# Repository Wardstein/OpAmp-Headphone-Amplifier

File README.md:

# Headphone Amplifier with 24bit DAC
A (massive) parallel OpAmp headphone amplifier using 16 parallel OpAmps per channel. The complete box has three PCBs: the power supply, a 24bit DAC with USB interface and the amplifier board itself (hidden under the black heatsink).

The amplifier PSU "base board" has an input for analog signals which can be routed to the amp board, or there can be a USB DAC board plugged in. When you want to switch between analog and USB input, you need to solder a switch to the base board connections of the DAC board (see in the pictures above).

# Noise
The reasoning behind the paralleling so much opamps is to decrease the noise during amplification and therefore improve the SNR. When using this headphone amp with the USB DAC board, we want to give some credit to the 24bit DAC and make the amp as low noise as possible.

In theory the noise is multiplied by the square root of N (number of amplifiers), instead of the number of amplifiers like the gain. Here is a good read: https://www.analog.com/en/technical-articles/paralleling-amplifiers-improves-signal-to-noise-performance.html

This is also the reasoning for the torodial transformer and the linear power supply.

One drawback of the parallel OpAmps is the waste heat, generated by the chips as they are driving their outputs against each other. Typically audio amplifiers are not "high precision" amps in terms of DC offset voltages, so each OpAmp has a different offset and therefore they all drive a bit of current all the time.

# Setting up the CP2114-B02 USB-I2S Bridge chip
Poorly the CP2114-B02 is also obsolete and I could not find any other replacement chip for USB to I2S which offers 24bit support. ONLY the -B02 version offers 24bit support. Maybe one can replace it with some Cypress FX2/FX3 chips or an AVR/SAM with a USB audio device firmware.

Anyways, how to configure the existing CP2114-B02: It has a One-Time Programmable ROM (chapter 3.6 in the datasheet), where config slots can be programmed with a PC tool. These slots contain information about clocking, audio data format and so on. The config is selected at startup by some bootstrapping pins, which means we do not have to configure the CP2114 with an MCU after we programmed it with the PC.

Steps to program the config:

1. Extract the PC utility called CP21xxCustomizationUtility from AN721SW.zip file, for your operating system
2. Connect the DAC board/the CP2114 via USB and power it up (could be in this headphone amplifier, or in your custom circuit)
3. Load the finished configuration from the file "ConfigData_24bit.txt" and click the "Program Device" button.

Ensure you selected the right config at the first time of programming, as each slot can only be written once. The next program cycle will write to the next slot, and you have to change then the config bootstrapping pin resistors to select the right config slot at startup!

After programming the chip, you need to uninstall it in the device manager and replug it, at least under windows, to make the new config take effect.

Some link collection used during the config creation:

* Only 24bit playback or recording at a time:
  * https://community.silabs.com/s/article/cp2114-b02-24-bit-record-playback-vs-16-bit-record-playback?language=en_US
  * https://community.silabs.com/s/article/cp2114-b02-audio-24-bit-mode?language=en_US
  * https://community.silabs.com/s/question/0D51M00007xeOMqSAM/does-the-cp2114b02-support-true-24-bits?language=en_US
* Bad noise (happend to me also), taken care in the config
  * https://community.silabs.com/s/question/0D51M00007xeE9cSAE/cp2114-crackling-or-choppy-noise?language=en_US
  * https://community.silabs.com/s/article/cp2114-and-asynchronous-mode?language=en_US
  * https://www.silabs.com/documents/public/errata/cp2114-errata.pdf chapter 3.2.1
* Distinguishing chip version: https://community.silabs.com/s/article/cp2114-b01-vs-b02-package-marking-1?language=en_US

# Replacement for the obsolete OPA2604
The internet delivers multiple alternatives for the obsolete OPA2604:
* OPA2134 (need to make sure the PSU PCB is tuned to +-15V!)
* OPA2227 (need to make sure the PSU PCB is tuned to +-15V!)
* OPA1642
* NE5534A (not a double opamp, not pin compatible)

Source: http://www.hifi-forum.de/viewthread-71-13538.html (german). Also with some good noise comparison charts.

# Housing

The housing is a proMa "Euro-Gehäuse EG 1" article number "131 020", e.g. available at [Reichelt](https://www.reichelt.de/de/en/euro-casing-geh-eg-1-p50423.html). The front and back are custom 3D prints. The front panel PCB is also custom made exactly for this housing, but is fairly easy modified for any other housing front.

# License
The content of this whole repository is licensed under [CERN-OHL-W v2](License/cern_ohl_w_v2.txt) or later by Jonas Eberhard.

Excepted is the software copied from Cypress in the AN721SW.zip file. This was copied to this repo for archiving purpose!

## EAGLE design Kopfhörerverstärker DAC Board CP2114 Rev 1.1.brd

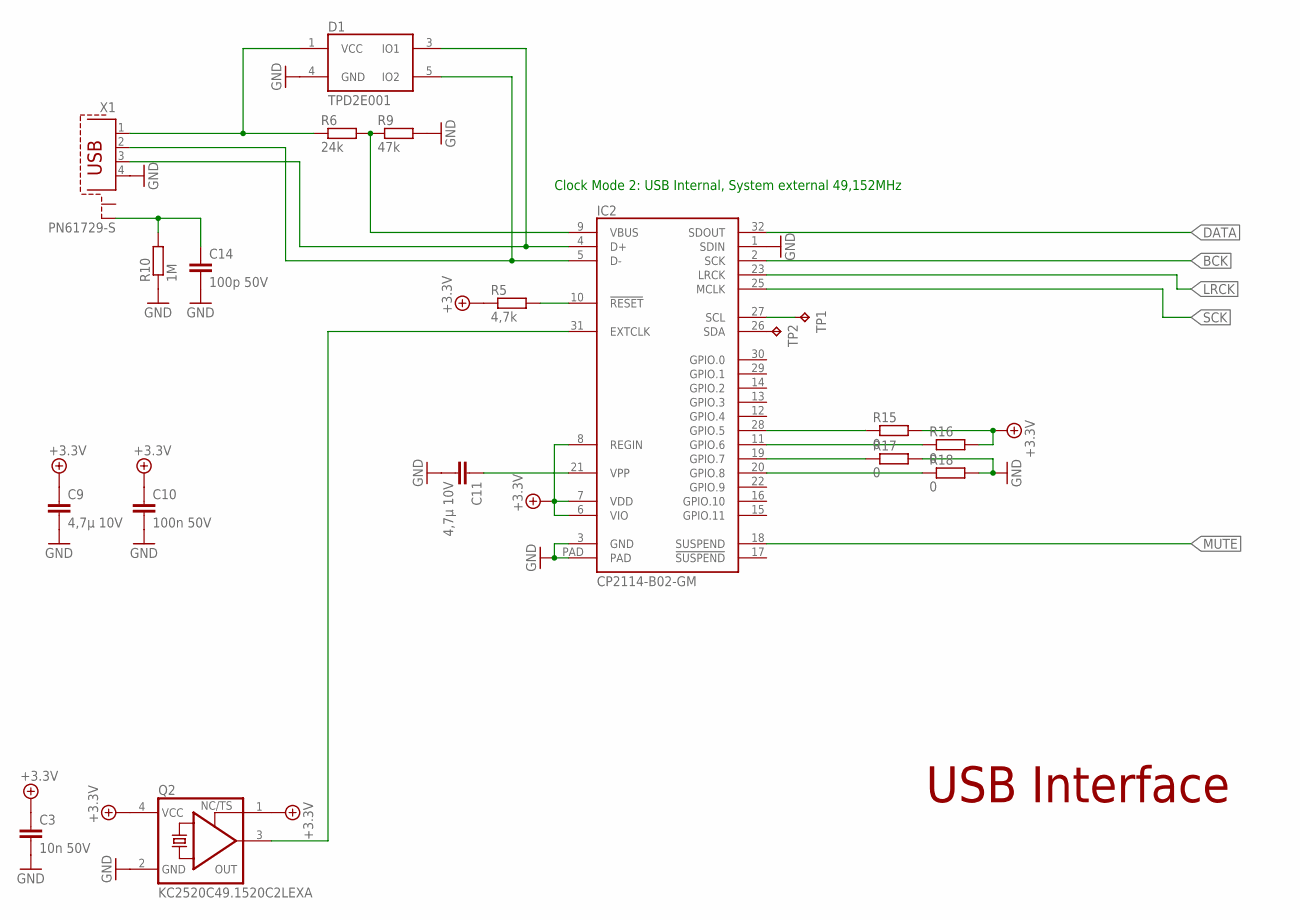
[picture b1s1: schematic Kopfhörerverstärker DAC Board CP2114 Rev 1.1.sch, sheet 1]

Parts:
C3: 10n 50V; C0805
C9, C11: 4,7µ 10V; C0805
C10: 100n 50V; C0805
C14: 100p 50V; C0805
D1: TPD2E001; SOT-5X3_R-PDSO-N5-DRL
IC2: CP2114-B02-GM; QFN32
Q2: KC2520C49.1520C2LEXA; 2.5X2.0
R5: 4,7k; R0805
R6: 24k; R0805
R9: 47k; R0805
R10: 1M; R0805
R15, R16, R17, R18: 0; R0805
TP1, TP2: TPTP10R; TP10R
X1: PN61729-S

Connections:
+3,3V: C3.1, C9.1, C10.1, IC2.6 (VIO), IC2.7 (VDD), IC2.8 (REGIN), Q2.1 (TS), Q2.4 (VCC), R5.1, R15.2, R16.2; also elsewhere on the board
BCK: IC2.2 (SCK); also elsewhere on the board
DATA: IC2.32 (SDOUT); also elsewhere on the board
GND: C3.2, C9.2, C10.2, C11.2, C14.2, D1.4 (GND), IC2.1 (SDIN), IC2.3 (GND), IC2.PAD, Q2.2 (GND), R9.2, R10.1, R17.2, R18.2, X1.4; also elsewhere on the board
LRCK: IC2.23 (LRCK); also elsewhere on the board
MUTE: IC2.18 (SUSPEND); also elsewhere on the board
unnamed: IC2.28 (GPIO.5), R15.1
unnamed: IC2.31 (EXTCLK), Q2.3 (OUT)
unnamed: IC2.9 (VBUS), R6.2, R9.1
unnamed: C11.1, IC2.21 (VPP)
unnamed: IC2.10 (!RESET), R5.2
unnamed: C14.1, R10.2, X1.S2
unnamed: D1.5 (IO2), IC2.5 (D-), X1.2
unnamed: D1.3 (IO1), IC2.4 (D+), X1.3
unnamed: D1.1 (VCC), R6.1, X1.1
unnamed: IC2.27 (SCL), TP1.TP
unnamed: IC2.26 (SDA), TP2.TP
unnamed: IC2.11 (GPIO.6), R16.1
unnamed: IC2.19 (GPIO.7), R17.1
unnamed: IC2.20 (GPIO.8), R18.1
SCK: IC2.25 (MCLK); also elsewhere on the board

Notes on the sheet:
USB Interface
Clock Mode 2: USB Internal, System external 49,152MHz

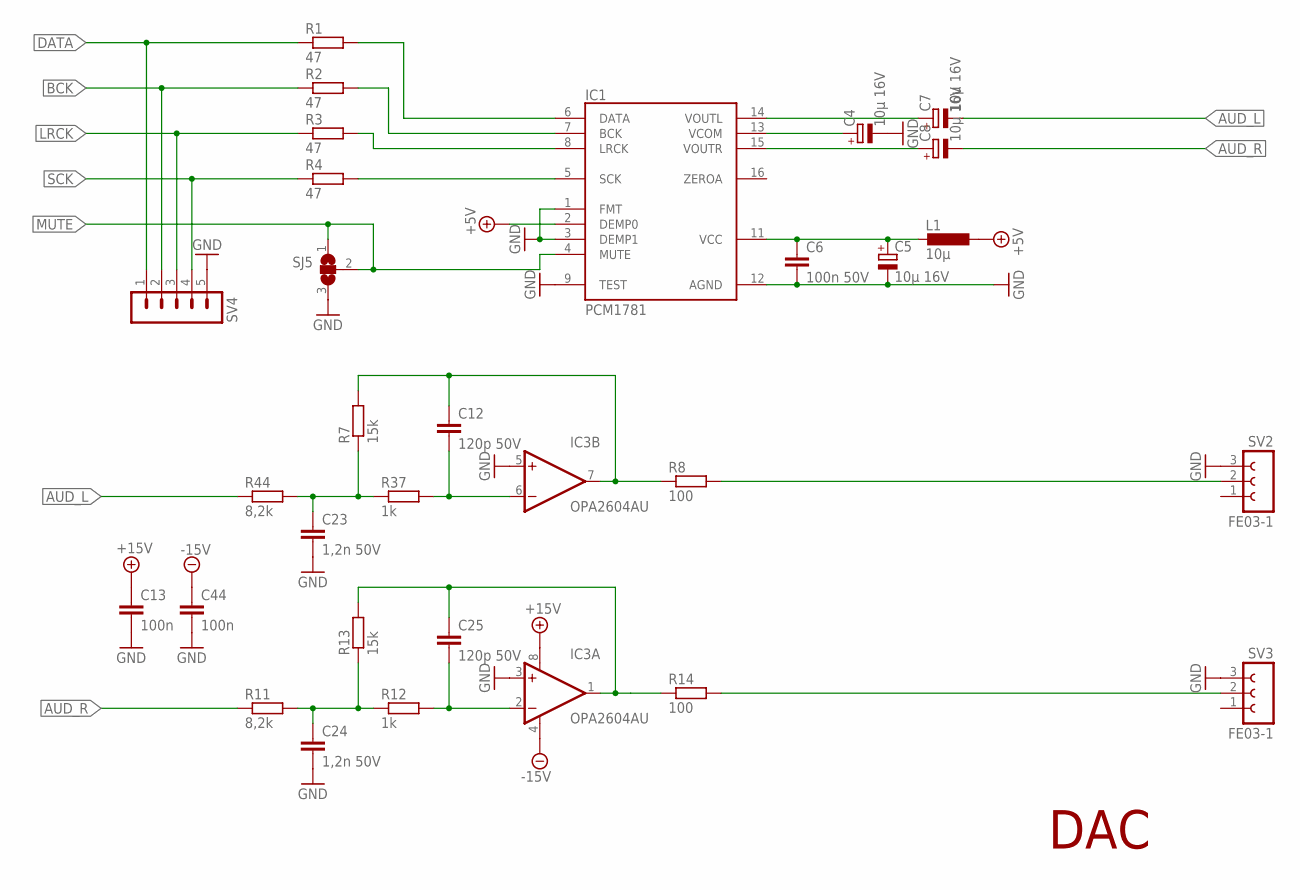
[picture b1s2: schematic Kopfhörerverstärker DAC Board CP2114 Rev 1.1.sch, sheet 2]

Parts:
C4, C5, C7, C8: 10µ 16V; E2,5-5
C6: 100n 50V; C0805
C12, C25: 120p 50V; C0805
C13, C44: 100n; C0805
C23, C24: 1,2n 50V; C0805
IC1: PCM1781; PW_R-PDSO-G16
IC3: OPA2604AU; SO08
L1: 10µ; L0805
R1, R2, R3, R4: 47; R0805
R7, R13: 15k; R0805
R8, R14: 100; R0805
R11, R44: 8,2k; R0805
R12, R37: 1k; R0805
SJ5: SJ2W; SJ_2
SV2, SV3: FE03-1
SV4: MA05-1

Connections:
+5V: IC1.2 (DEMP0), L1.1; also elsewhere on the board
+15V: C13.1, IC3.8 (V+); also elsewhere on the board
-15V: C44.1, IC3.4 (V-); also elsewhere on the board
AUD_L: C7.-, R44.1
AUD_R: C8.-, R11.1
BCK: R2.1, SV4.2; also elsewhere on the board
DATA: R1.1, SV4.1; also elsewhere on the board
GND: C4.-, C5.-, C6.2, C13.2, C23.2, C24.2, C44.2, IC1.1 (FMT), IC1.3 (DEMP1), IC1.9 (TEST), IC1.12 (AGND), IC3.3 (+IN), IC3.5 (+IN), SJ5.3, SV2.3, SV3.3, SV4.5; also elsewhere on the board
LRCK: R3.1, SV4.3; also elsewhere on the board
MUTE: IC1.4 (MUTE), SJ5.1, SJ5.2; also elsewhere on the board
unnamed: C23.1, R7.1, R37.1, R44.2
unnamed: C8.+, IC1.15 (VOUTR)
unnamed: C7.+, IC1.14 (VOUTL)
unnamed: IC1.6 (DATA), R1.2
unnamed: IC1.7 (BCK), R2.2
unnamed: IC1.8 (LRCK), R3.2
unnamed: IC1.5 (SCK), R4.2
unnamed: C5.+, C6.1, IC1.11 (VCC), L1.2
unnamed: C4.+, IC1.13 (VCOM)
unnamed: C25.1, IC3.1 (OUT), R13.2, R14.1
unnamed: R14.2, SV3.2
unnamed: C12.2, IC3.6 (-IN), R37.2
unnamed: C12.1, IC3.7 (OUT), R7.2, R8.1
unnamed: R8.2, SV2.2
unnamed: C25.2, IC3.2 (-IN), R12.2
unnamed: C24.1, R11.2, R12.1, R13.1
SCK: R4.1, SV4.4; also elsewhere on the board

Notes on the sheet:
DAC

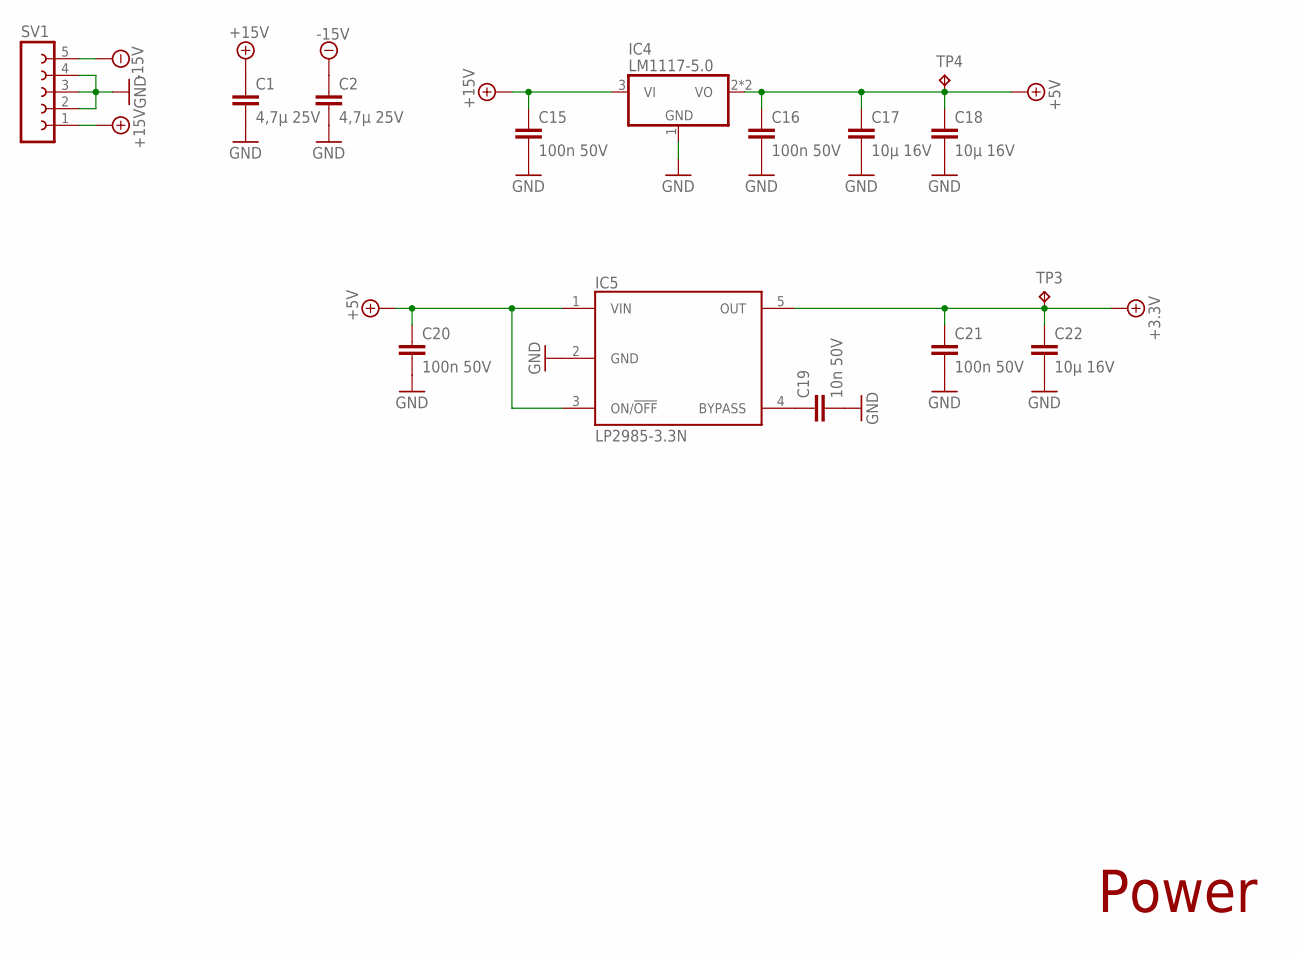
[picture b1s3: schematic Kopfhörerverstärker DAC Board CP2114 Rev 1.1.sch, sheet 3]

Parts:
C1, C2: 4,7µ 25V; C0805
C15, C16, C20, C21: 100n 50V; C0805
C17, C18, C22: 10µ 16V; C0805
C19: 10n 50V; C0805
IC4: LM1117-5.0; SOT223
IC5: LP2985-3.3N; SOT23-DBV
SV1: FE05-1
TP3, TP4: TPTP15R; TP15R

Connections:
+3,3V: C21.1, C22.1, IC5.5 (OUT), TP3.TP; also elsewhere on the board
+5V: C16.1, C17.1, C18.1, C20.1, IC4.2 (VO), IC4.4 (VO), IC5.1 (VIN), IC5.3 (ON/!OFF), TP4.TP; also elsewhere on the board
+15V: C1.1, C15.1, IC4.3 (VI), SV1.1; also elsewhere on the board
-15V: C2.1, SV1.5; also elsewhere on the board
GND: C1.2, C2.2, C15.2, C16.2, C17.2, C18.2, C19.2, C20.2, C21.2, C22.2, IC4.1 (GND), IC5.2 (GND), SV1.2, SV1.3, SV1.4; also elsewhere on the board
unnamed: C19.1, IC5.4 (BYPASS)

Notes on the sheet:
Power

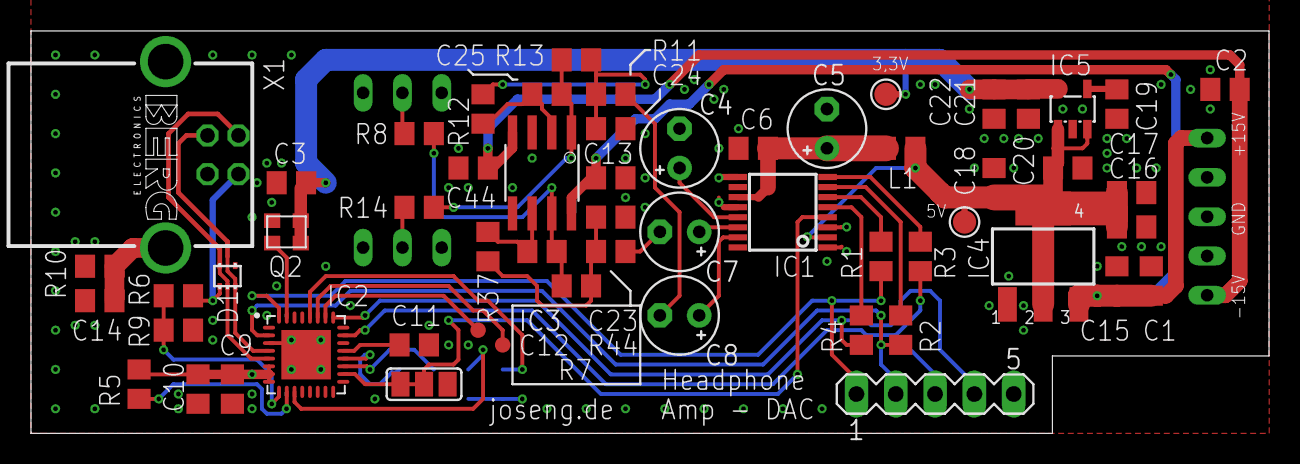
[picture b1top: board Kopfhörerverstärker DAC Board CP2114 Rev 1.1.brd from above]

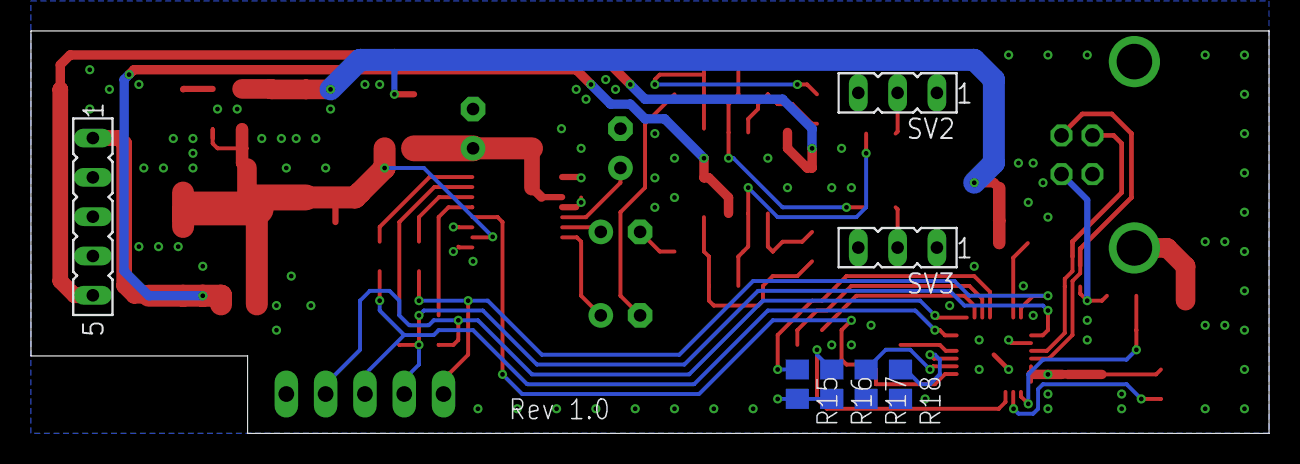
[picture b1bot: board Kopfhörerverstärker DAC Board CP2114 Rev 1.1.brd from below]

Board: 4 copper layers, 80.0 x 26.0 mm, 64 parts (7 on the bottom side), 43 nets.

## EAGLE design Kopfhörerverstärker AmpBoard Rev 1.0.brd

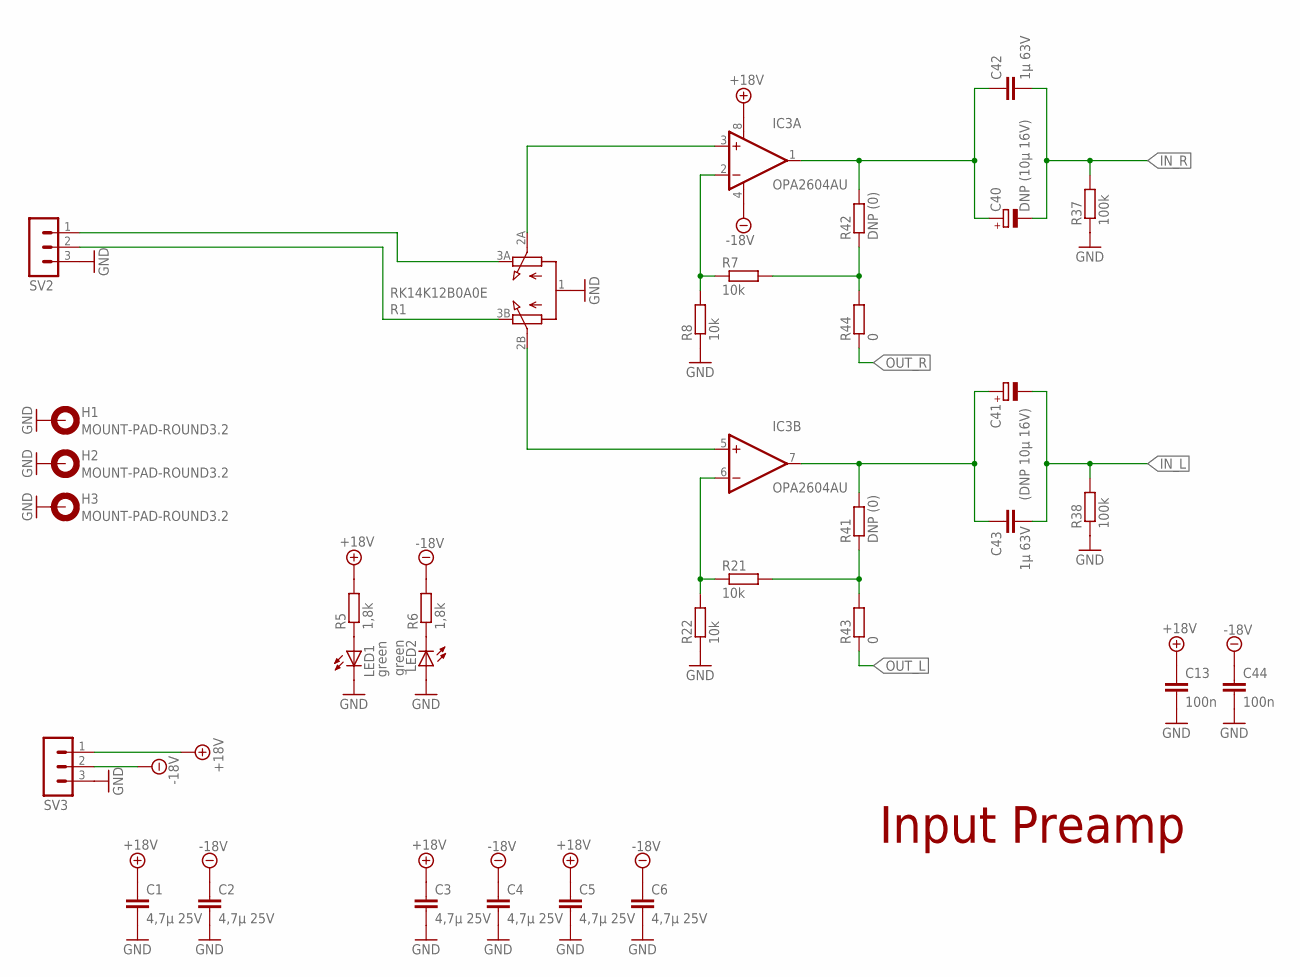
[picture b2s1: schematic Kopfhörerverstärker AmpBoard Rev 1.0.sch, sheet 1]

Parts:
C1, C2, C3, C4, C5, C6: 4,7µ 25V; C0805
C13, C44: 100n; C0805
C40: DNP (10µ 16V); E2,5-5
C41: (DNP 10µ 16V); E2,5-5
C42, C43: 1µ 63V; C050-050X075
H1, H2, H3: MOUNT-PAD-ROUND3.2; 3,2-PAD
IC3: OPA2604AU; SO08
LED1, LED2: green; LED3MM
R1: RK14K12B0A0E; RK14K12
R5, R6: 1,8k; R0805
R7, R8, R21, R22: 10k; R0805
R37, R38: 100k; R0805
R41, R42: DNP (0); R0805
R43, R44: 0; R0805
SV2, SV3: MA03-1

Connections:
+18V: C1.1, C3.1, C5.1, C13.1, IC3.8 (V+), R5.2, SV3.1; also elsewhere on the board
-18V: C2.1, C4.1, C6.1, C44.1, IC3.4 (V-), R6.2, SV3.2; also elsewhere on the board
GND: C1.2, C2.2, C3.2, C4.2, C5.2, C6.2, C13.2, C44.2, H1.B3,2, H2.B3,2, H3.B3,2, LED1.K (C), LED2.A, R1.1, R8.1, R22.1, R37.1, R38.1, SV2.3, SV3.3; also elsewhere on the board
IN_L: C41.-, C43.2, R38.2; also elsewhere on the board
IN_R: C40.-, C42.2, R37.2; also elsewhere on the board
unnamed: R1.3A, SV2.1
unnamed: R1.3B, SV2.2
unnamed: LED1.A, R5.1
unnamed: LED2.K (C), R6.1
unnamed: IC3.2 (-IN), R7.1, R8.2
unnamed: C40.+, C42.1, IC3.1 (OUT), R42.2
unnamed: IC3.6 (-IN), R21.1, R22.2
unnamed: IC3.5 (+IN), R1.2B
unnamed: IC3.3 (+IN), R1.2A
unnamed: R21.2, R41.1, R43.2
unnamed: R7.2, R42.1, R44.2
unnamed: C41.+, C43.1, IC3.7 (OUT), R41.2
OUT_L: R43.1; also elsewhere on the board
OUT_R: R44.1; also elsewhere on the board

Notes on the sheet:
Input Preamp

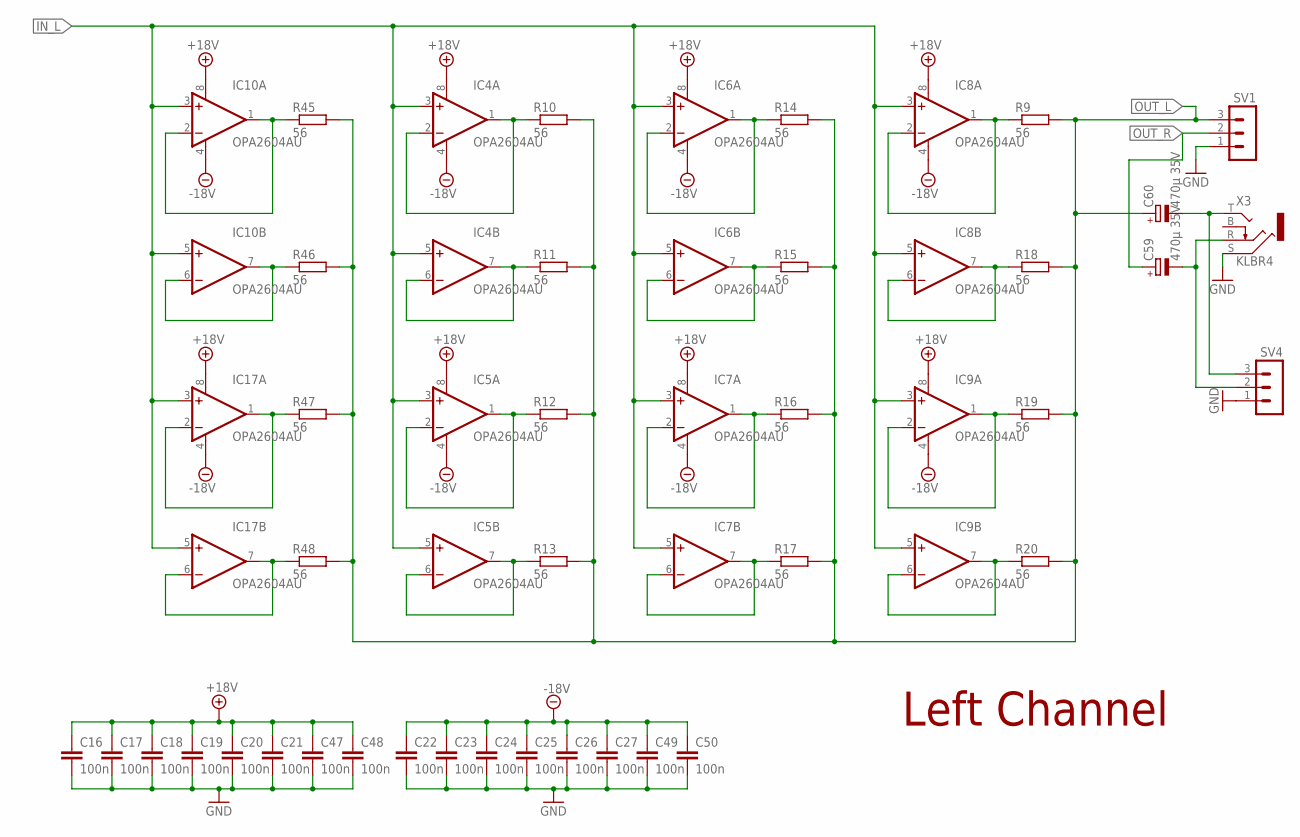
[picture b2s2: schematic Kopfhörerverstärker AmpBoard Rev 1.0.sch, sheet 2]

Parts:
C16, C17, C18, C19, C20, C21, C22, C23, C24, C25, C26, C27, C47, C48, C49, C50: 100n; C0805
C59, C60: 470µ 35V; E5-10,5
IC4, IC5, IC6, IC7, IC8, IC9, IC10, IC17: OPA2604AU; SO08
R9, R10, R11, R12, R13, R14, R15, R16, R17, R18, R19, R20, R45, R46, R47, R48: 56; R0805
SV1, SV4: MA03-1
X3: KLBR4

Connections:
+18V: C16.1, C17.1, C18.1, C19.1, C20.1, C21.1, C47.1, C48.1, IC4.8 (V+), IC5.8 (V+), IC6.8 (V+), IC7.8 (V+), IC8.8 (V+), IC9.8 (V+), IC10.8 (V+), IC17.8 (V+); also elsewhere on the board
-18V: C22.1, C23.1, C24.1, C25.1, C26.1, C27.1, C49.1, C50.1, IC4.4 (V-), IC5.4 (V-), IC6.4 (V-), IC7.4 (V-), IC8.4 (V-), IC9.4 (V-), IC10.4 (V-), IC17.4 (V-); also elsewhere on the board
GND: C16.2, C17.2, C18.2, C19.2, C20.2, C21.2, C22.2, C23.2, C24.2, C25.2, C26.2, C27.2, C47.2, C48.2, C49.2, C50.2, SV1.1, SV4.1, X3.S; also elsewhere on the board
IN_L: IC4.3 (+IN), IC4.5 (+IN), IC5.3 (+IN), IC5.5 (+IN), IC6.3 (+IN), IC6.5 (+IN), IC7.3 (+IN), IC7.5 (+IN), IC8.3 (+IN), IC8.5 (+IN), IC9.3 (+IN), IC9.5 (+IN), IC10.3 (+IN), IC10.5 (+IN), IC17.3 (+IN), IC17.5 (+IN); also elsewhere on the board
unnamed: C59.-, SV4.2, X3.R
unnamed: C60.-, SV4.3, X3.T
unnamed: IC4.6 (-IN), IC4.7 (OUT), R11.1
unnamed: IC5.1 (OUT), IC5.2 (-IN), R12.1
unnamed: IC8.1 (OUT), IC8.2 (-IN), R9.1
unnamed: IC4.1 (OUT), IC4.2 (-IN), R10.1
unnamed: IC5.6 (-IN), IC5.7 (OUT), R13.1
unnamed: IC6.1 (OUT), IC6.2 (-IN), R14.1
unnamed: IC6.6 (-IN), IC6.7 (OUT), R15.1
unnamed: IC7.1 (OUT), IC7.2 (-IN), R16.1
unnamed: IC7.6 (-IN), IC7.7 (OUT), R17.1
unnamed: IC8.6 (-IN), IC8.7 (OUT), R18.1
unnamed: IC9.1 (OUT), IC9.2 (-IN), R19.1
unnamed: IC9.6 (-IN), IC9.7 (OUT), R20.1
unnamed: IC10.1 (OUT), IC10.2 (-IN), R45.1
unnamed: IC10.6 (-IN), IC10.7 (OUT), R46.1
unnamed: IC17.1 (OUT), IC17.2 (-IN), R47.1
unnamed: IC17.6 (-IN), IC17.7 (OUT), R48.1
OUT_L: C60.+, R9.2, R10.2, R11.2, R12.2, R13.2, R14.2, R15.2, R16.2, R17.2, R18.2, R19.2, R20.2, R45.2, R46.2, R47.2, R48.2, SV1.3; also elsewhere on the board
OUT_R: C59.+, SV1.2; also elsewhere on the board

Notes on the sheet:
Left Channel

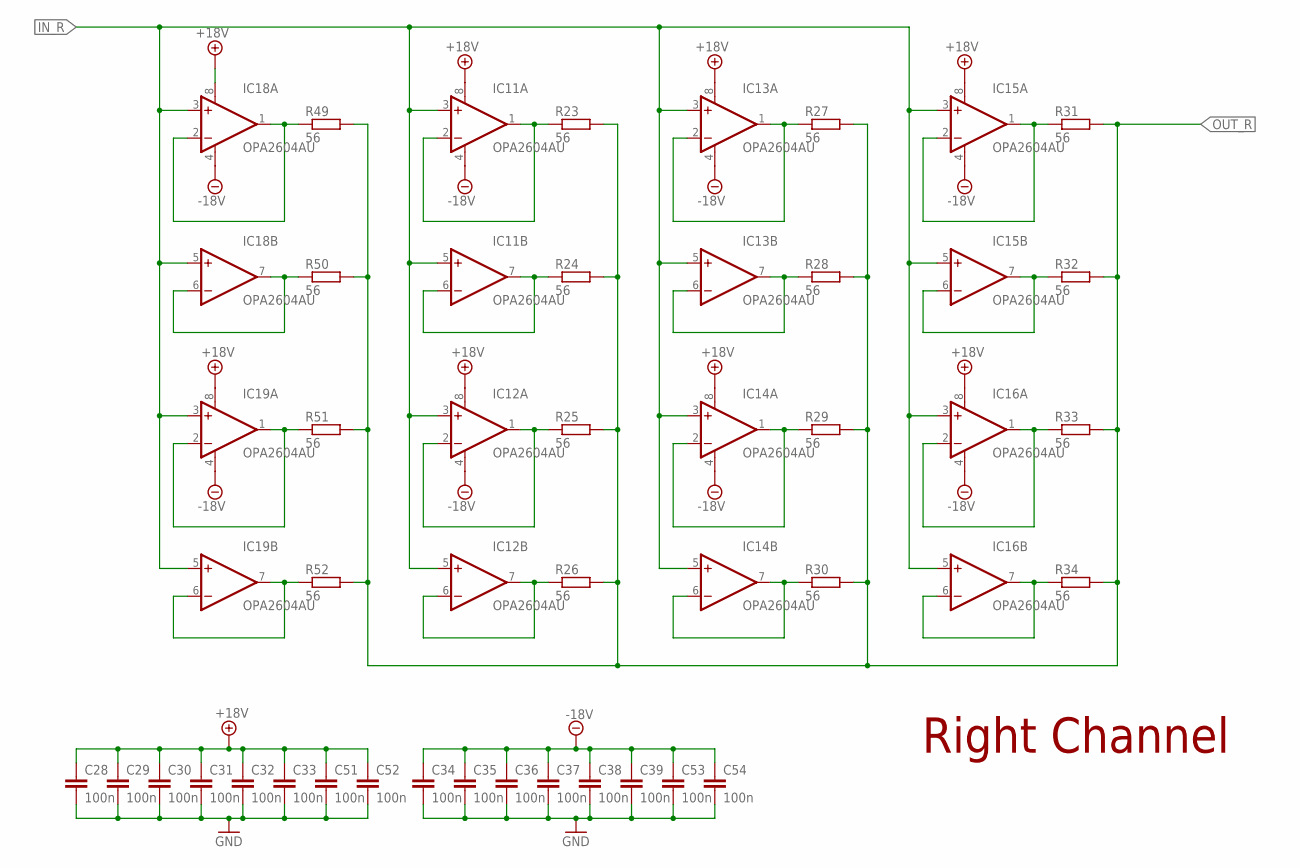
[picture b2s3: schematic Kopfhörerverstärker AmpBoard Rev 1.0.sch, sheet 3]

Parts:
C28, C29, C30, C31, C32, C33, C34, C35, C36, C37, C38, C39, C51, C52, C53, C54: 100n; C0805
IC11, IC12, IC13, IC14, IC15, IC16, IC18, IC19: OPA2604AU; SO08
R23, R24, R25, R26, R27, R28, R29, R30, R31, R32, R33, R34, R49, R50, R51, R52: 56; R0805

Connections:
+18V: C28.1, C29.1, C30.1, C31.1, C32.1, C33.1, C51.1, C52.1, IC11.8 (V+), IC12.8 (V+), IC13.8 (V+), IC14.8 (V+), IC15.8 (V+), IC16.8 (V+), IC18.8 (V+), IC19.8 (V+); also elsewhere on the board
-18V: C34.1, C35.1, C36.1, C37.1, C38.1, C39.1, C53.1, C54.1, IC11.4 (V-), IC12.4 (V-), IC13.4 (V-), IC14.4 (V-), IC15.4 (V-), IC16.4 (V-), IC18.4 (V-), IC19.4 (V-); also elsewhere on the board
GND: C28.2, C29.2, C30.2, C31.2, C32.2, C33.2, C34.2, C35.2, C36.2, C37.2, C38.2, C39.2, C51.2, C52.2, C53.2, C54.2; also elsewhere on the board
IN_R: IC11.3 (+IN), IC11.5 (+IN), IC12.3 (+IN), IC12.5 (+IN), IC13.3 (+IN), IC13.5 (+IN), IC14.3 (+IN), IC14.5 (+IN), IC15.3 (+IN), IC15.5 (+IN), IC16.3 (+IN), IC16.5 (+IN), IC18.3 (+IN), IC18.5 (+IN), IC19.3 (+IN), IC19.5 (+IN); also elsewhere on the board
unnamed: IC11.1 (OUT), IC11.2 (-IN), R23.1
unnamed: IC11.6 (-IN), IC11.7 (OUT), R24.1
unnamed: IC12.1 (OUT), IC12.2 (-IN), R25.1
unnamed: IC12.6 (-IN), IC12.7 (OUT), R26.1
unnamed: IC13.1 (OUT), IC13.2 (-IN), R27.1
unnamed: IC13.6 (-IN), IC13.7 (OUT), R28.1
unnamed: IC14.1 (OUT), IC14.2 (-IN), R29.1
unnamed: IC14.6 (-IN), IC14.7 (OUT), R30.1
unnamed: IC15.1 (OUT), IC15.2 (-IN), R31.1
unnamed: IC15.6 (-IN), IC15.7 (OUT), R32.1
unnamed: IC16.1 (OUT), IC16.2 (-IN), R33.1
unnamed: IC16.6 (-IN), IC16.7 (OUT), R34.1
unnamed: IC18.1 (OUT), IC18.2 (-IN), R49.1
unnamed: IC18.6 (-IN), IC18.7 (OUT), R50.1
unnamed: IC19.1 (OUT), IC19.2 (-IN), R51.1
unnamed: IC19.6 (-IN), IC19.7 (OUT), R52.1
OUT_R: R23.2, R24.2, R25.2, R26.2, R27.2, R28.2, R29.2, R30.2, R31.2, R32.2, R33.2, R34.2, R49.2, R50.2, R51.2, R52.2; also elsewhere on the board

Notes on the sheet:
Right Channel

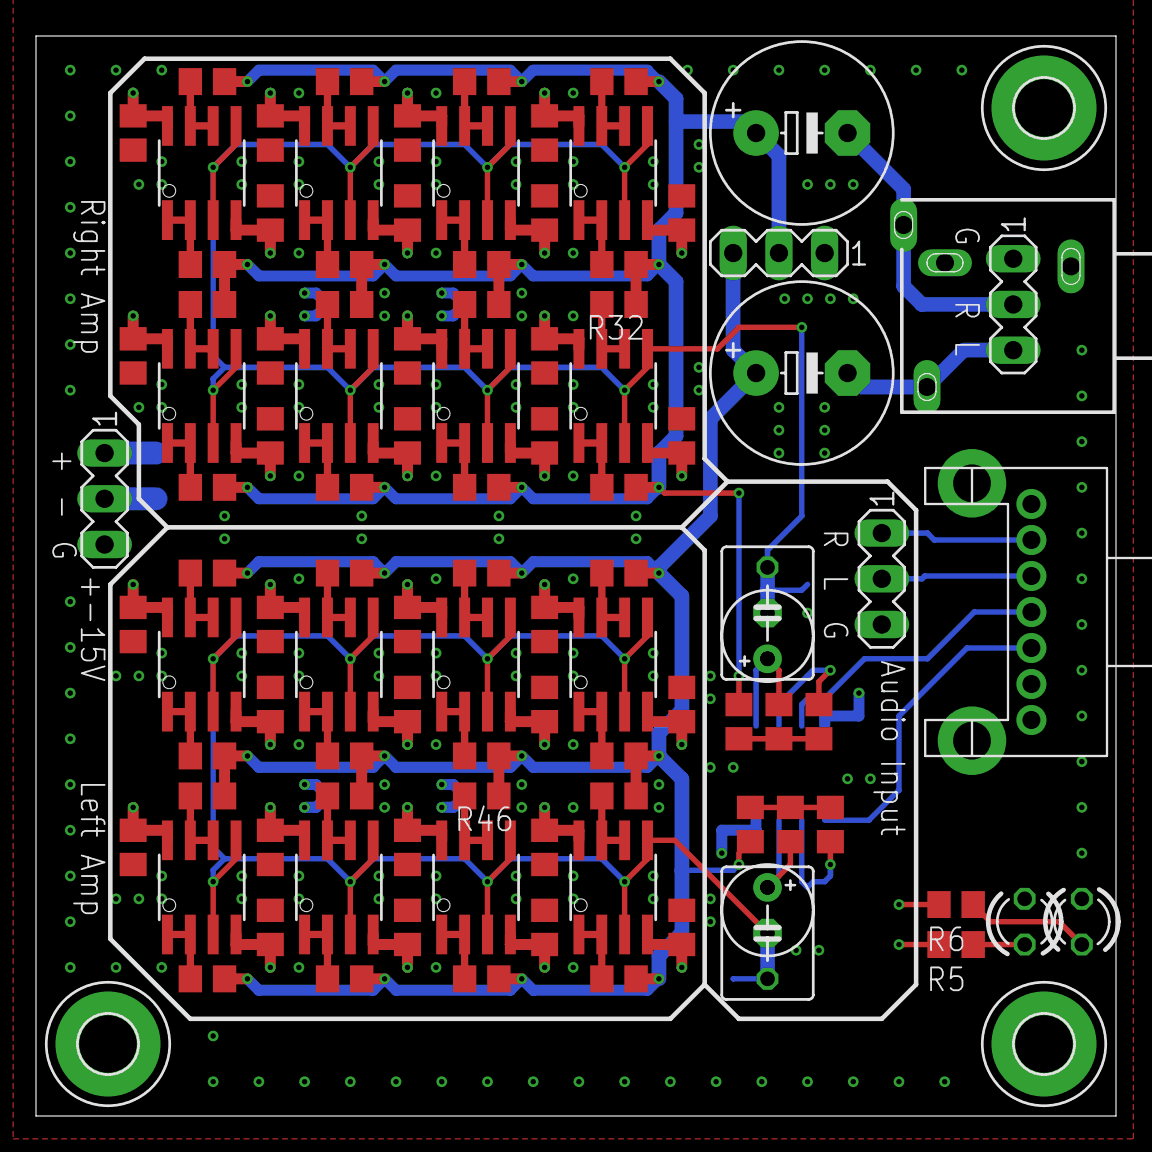
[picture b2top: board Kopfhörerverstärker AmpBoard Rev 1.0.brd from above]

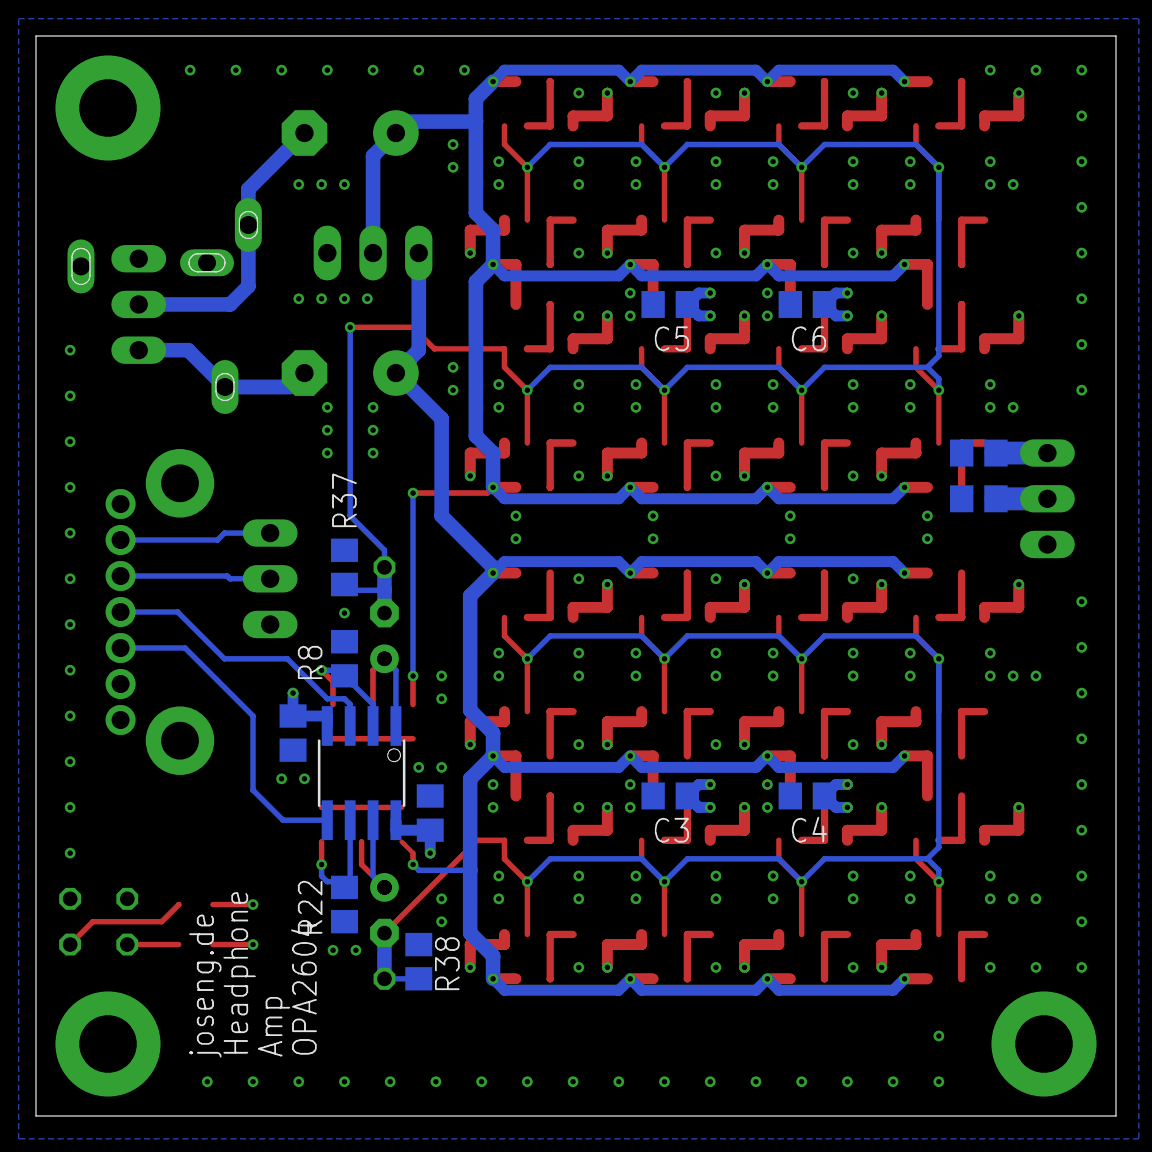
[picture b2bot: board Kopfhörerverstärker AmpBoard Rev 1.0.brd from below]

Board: 4 copper layers, 60.0 x 60.0 mm, 118 parts (13 on the bottom side), 53 nets.

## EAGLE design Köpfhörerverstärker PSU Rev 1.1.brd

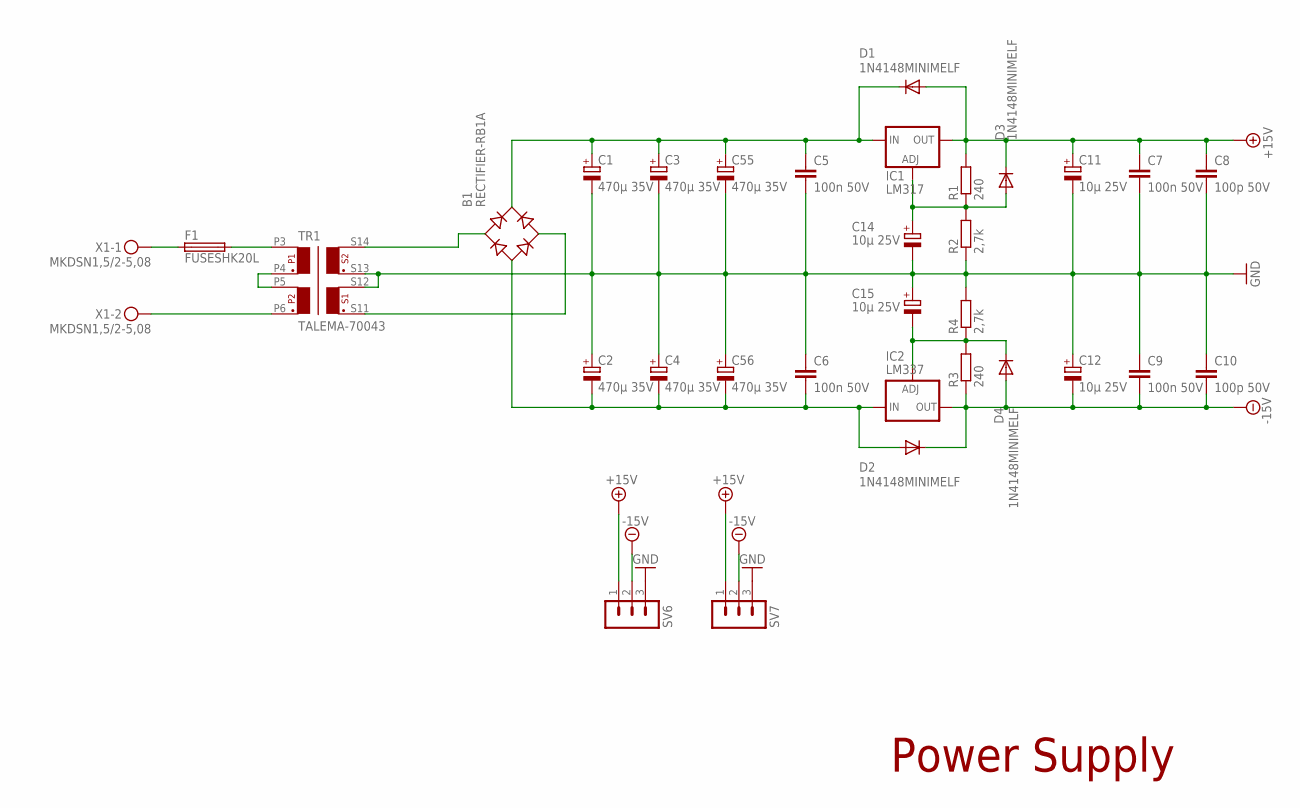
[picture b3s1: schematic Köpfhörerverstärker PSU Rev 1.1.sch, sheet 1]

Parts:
B1: RECTIFIER-RB1A; RB1A
C1, C2, C3, C4, C55, C56: 470µ 35V; E5-10,5
C5, C6, C7, C9: 100n 50V; C0805
C8, C10: 100p 50V; C0805
C11, C12, C14, C15: 10µ 25V; E2,5-5
D1, D2, D3, D4: 1N4148MINIMELF; MINIMELF
F1: FUSESHK20L; SHK20L
IC1: LM317; 317TL
IC2: LM337; 337TL
R1, R3: 240; R0805
R2, R4: 2,7k; R0805
SV6, SV7: MA03-1
TR1: TALEMA-70043
X1: MKDSN1,5/2-5,08

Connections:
+15V: C7.1, C8.1, C11.+, D1.A, D3.C, IC1.2 (OUT), R1.2, SV6.1, SV7.1; also elsewhere on the board
-15V: C9.2, C10.2, C12.-, D2.C, D4.A, IC2.3 (OUT), R3.1, SV6.2, SV7.2; also elsewhere on the board
GND: C1.-, C2.+, C3.-, C4.+, C5.2, C6.1, C7.2, C8.2, C9.1, C10.1, C11.-, C12.+, C14.-, C15.+, C55.-, C56.+, R2.1, R4.2, SV6.3, SV7.3, TR1.S12 (6), TR1.S13 (7); also elsewhere on the board
unnamed: F1.2A (2), TR1.P3 (1)
unnamed: F1.1A (1), X1.1
unnamed: TR1.P6 (4), X1.2
unnamed: TR1.P4 (2), TR1.P5 (3)
unnamed: B1.AC2, TR1.S11 (5)
unnamed: B1.AC1, TR1.S14 (8)
unnamed: C14.+, D3.A, IC1.1 (ADJ), R1.1, R2.2
unnamed: C15.-, D4.C, IC2.1 (ADJ), R3.2, R4.1
unnamed: B1.-, C2.-, C4.-, C6.2, C56.-, D2.A, IC2.2 (IN)
unnamed: B1.+, C1.+, C3.+, C5.1, C55.+, D1.C, IC1.3 (IN)

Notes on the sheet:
Power Supply

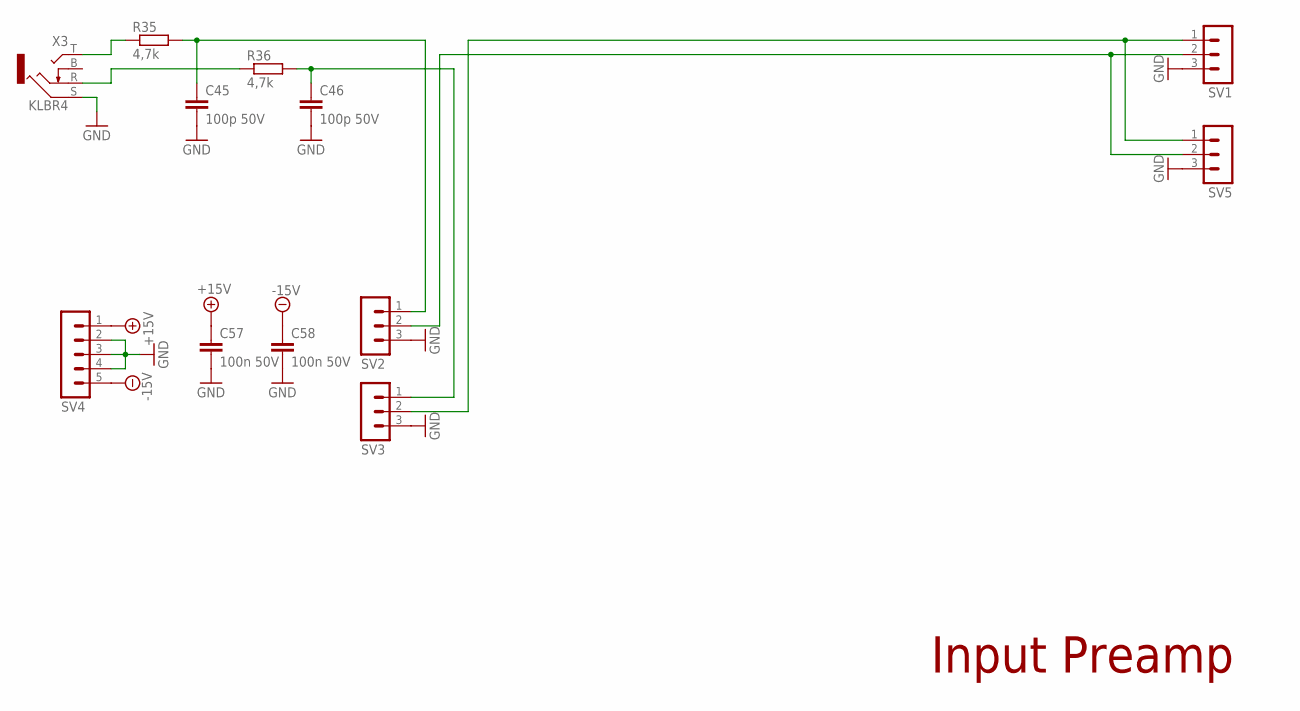
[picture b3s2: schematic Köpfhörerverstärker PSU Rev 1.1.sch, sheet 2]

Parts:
C45, C46: 100p 50V; C050-025X075
C57, C58: 100n 50V; C0805
R35, R36: 4,7k; R0805
SV1, SV2, SV3, SV5: MA03-1
SV4: MA05-1
X3: KLBR4

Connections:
+15V: C57.1, SV4.1; also elsewhere on the board
-15V: C58.1, SV4.5; also elsewhere on the board
GND: C45.2, C46.2, C57.2, C58.2, SV1.3, SV2.3, SV3.3, SV4.2, SV4.3, SV4.4, SV5.3, X3.S; also elsewhere on the board
unnamed: SV1.2, SV2.2, SV5.2
unnamed: R36.1, X3.R
unnamed: R35.1, X3.T
unnamed: C45.1, R35.2, SV2.1
unnamed: SV1.1, SV3.2, SV5.1
unnamed: C46.1, R36.2, SV3.1

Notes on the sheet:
Input Preamp
